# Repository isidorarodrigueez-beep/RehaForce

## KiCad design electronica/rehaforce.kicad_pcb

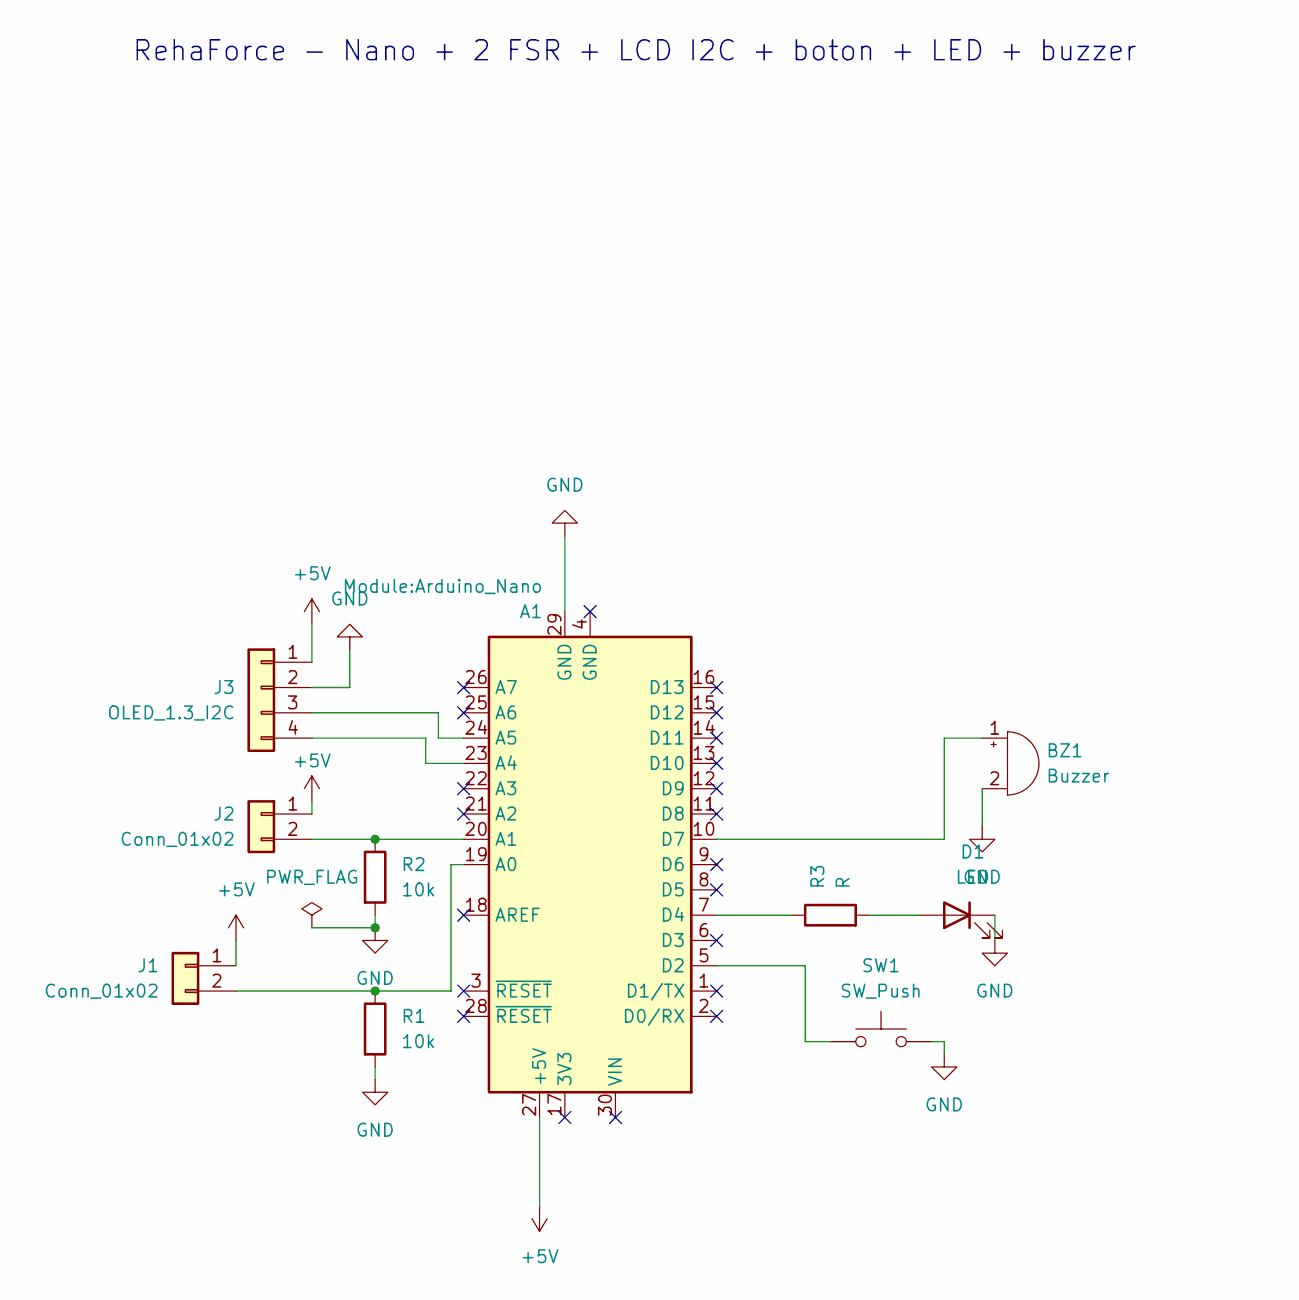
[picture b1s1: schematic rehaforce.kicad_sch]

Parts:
A1: Module:Arduino_Nano; Arduino_Nano
BZ1: Buzzer; Buzzer_12x9.5RM7.6
D1: LED; LED_D5.0mm
J1, J2: Conn_01x02; PinHeader_1x02_P2.54mm_Vertical
J3: OLED_1.3_I2C; PinHeader_1x04_P2.54mm_Vertical
R1, R2: 10k; R_Axial_DIN0207_L6.3mm_D2.5mm_P10.16mm_Horizontal
R3: R; R_Axial_DIN0207_L6.3mm_D2.5mm_P10.16mm_Horizontal
SW1: SW_Push; SW_PUSH_6mm

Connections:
+5V: A1.27 (+5V), J1.1, J2.1, J3.1
GND: A1.29 (GND), BZ1.2 (-), D1.1 (K), J3.2, R1.2, R2.2, SW1.2
unnamed: A1.19 (A0), J1.2, R1.1
unnamed: A1.20 (A1), J2.2, R2.1
unnamed: A1.23 (A4), J3.4
unnamed: A1.24 (A5), J3.3
unnamed: A1.5 (D2), SW1.1
unnamed: A1.7 (D4), R3.1
unnamed: A1.10 (D7), BZ1.1 (+)
unnamed: D1.2 (A), R3.2

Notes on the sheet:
RehaForce - Nano + 2 FSR + LCD I2C + boton + LED + buzzer

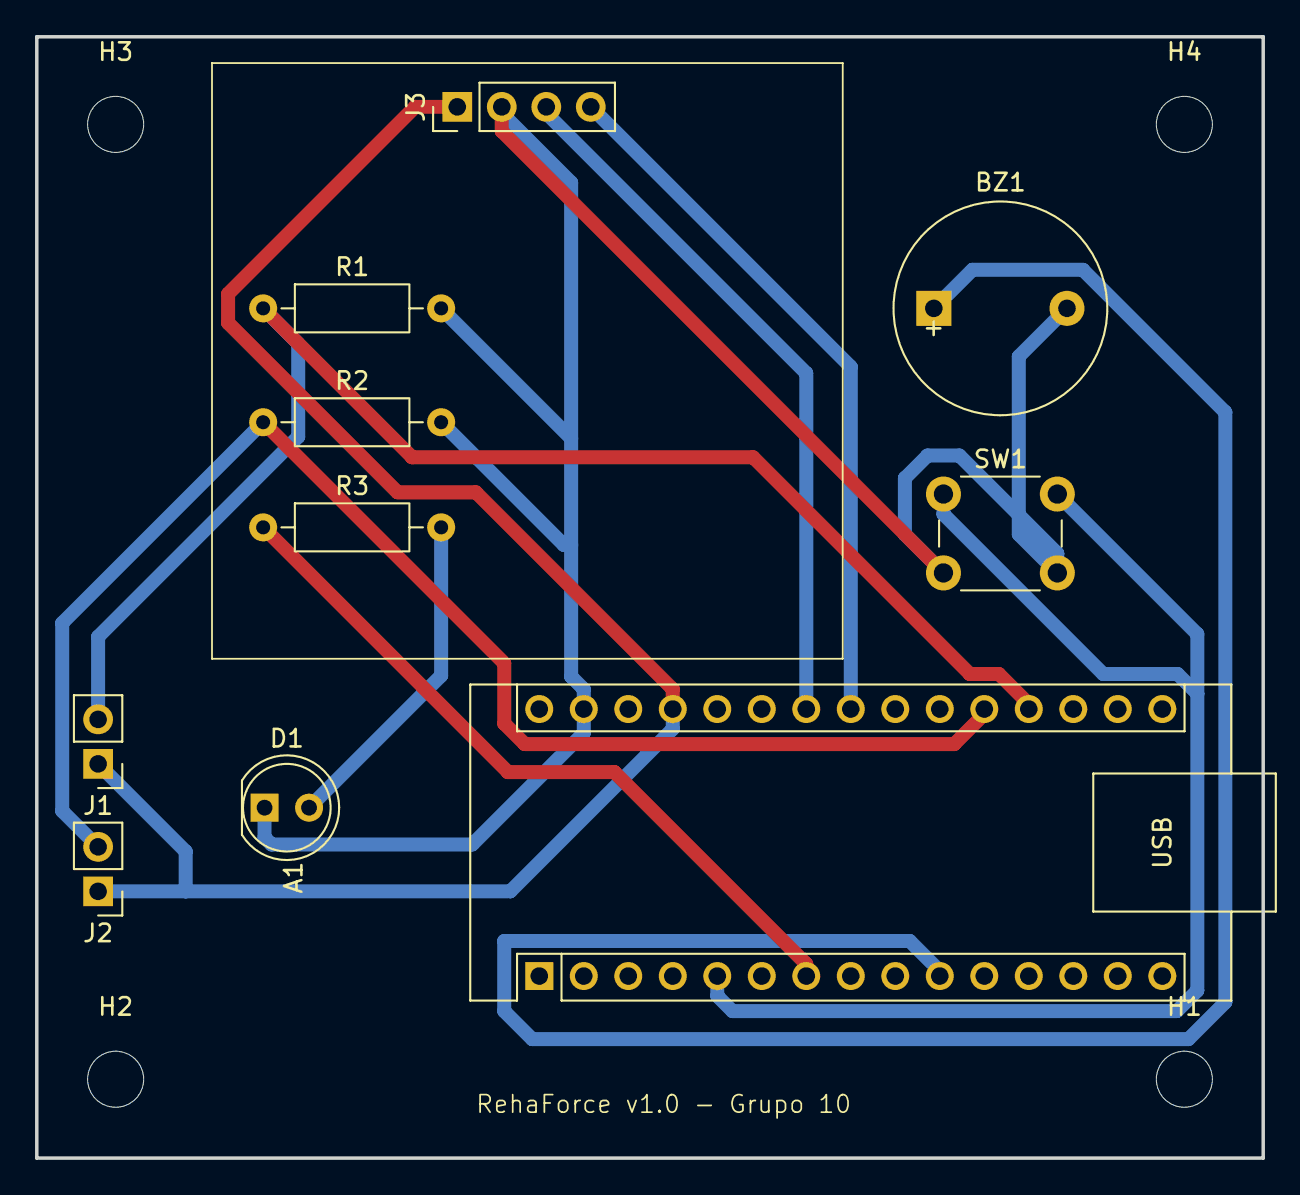
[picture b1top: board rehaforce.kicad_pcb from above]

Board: 2 copper layers, 70.0 x 64.0 mm, 14 parts (0 on the bottom side), 10 nets.

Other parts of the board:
H1, H2, H3, H4: MountingHole_3.2mm_M3
